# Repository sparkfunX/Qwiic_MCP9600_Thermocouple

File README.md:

SparkFun MCP9600 Thermocouple Amplifier
========================================

[*Thermocouple Amplifier (SPX-15508)*](https://www.sparkfun.com/products/15508)

The MCP9600 is an integrated thermocouple amplifier featuring a typical accuracy of ±0.5°C and a maximum accuracy of ±1.5°C, with support for many thermocouple types, conversion modes, and a configurable exponential moving average filter.

Repository Contents
-------------------

* **/Documentation** - Data sheets, additional product information
* **/Hardware** - Eagle design files (.brd, .sch)
* **/Production** - Production panel files (.brd)

Documentation
--------------
* **[SparkFun MCP9600 Arduino Library](https://github.com/sparkfun/SparkFun_MCP9600_Arduino_Library)** - Arduino library for the MCP9600.

License Information
-------------------

This product is _**open source**_! 

Please review the LICENSE.md file for license information. 

If you have any questions or concerns on licensing, please contact technical support on our [SparkFun forums](https://forum.sparkfun.com/viewforum.php?f=152).

Distributed as-is; no warranty is given.

- Your friends at SparkFun.

_<COLLABORATION CREDIT>_

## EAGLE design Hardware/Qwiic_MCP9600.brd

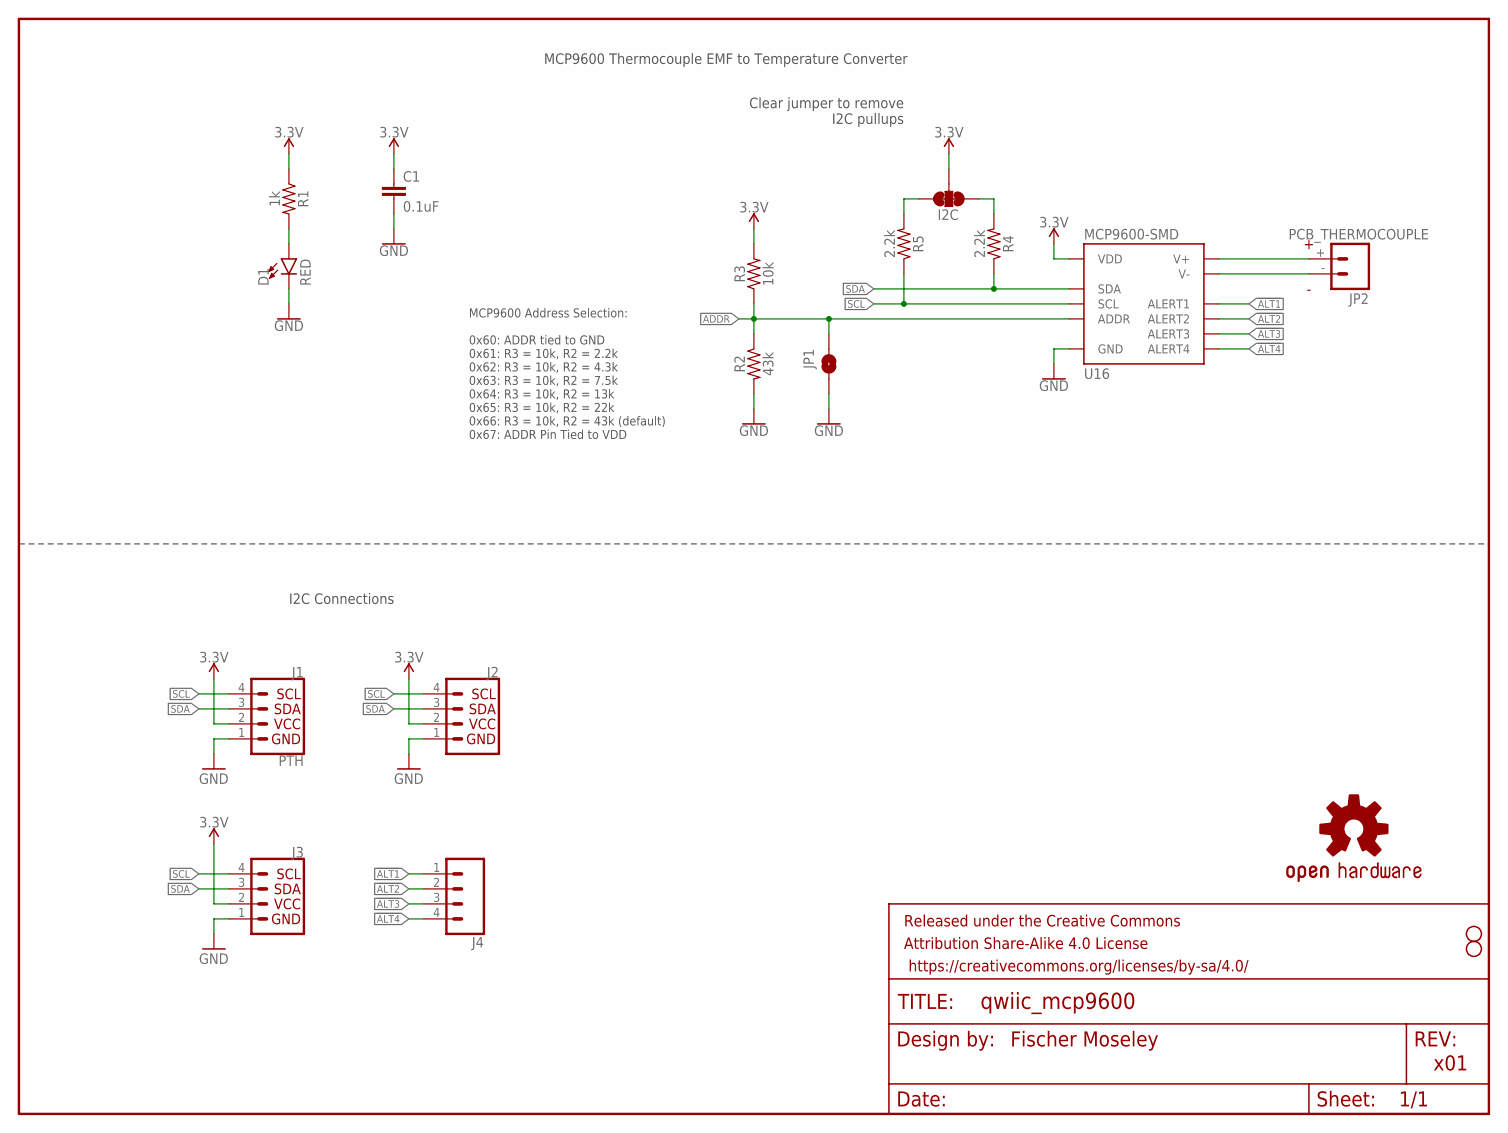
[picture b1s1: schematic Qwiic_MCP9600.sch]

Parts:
C1: 0.1uF; 0603
D1: RED; LED-0603
FRAME1: FRAME-LETTER; CREATIVE_COMMONS
I2C: JUMPER-SMT_3_2-NC_TRACE_SILK; SMT-JUMPER_3_2-NC_TRACE_SILK
J1: PTH; 1X04_NO_SILK
J2, J3: QWIIC_CONNECTORJS-1MM; JST04_1MM_RA
J4: CONN_041X04_NO_SILK; 1X04_NO_SILK
JP1: JUMPER-SMT_2_NO_SILK; SMT-JUMPER_2_NO_SILK
JP2: PCB_THERMOCOUPLE; PCC-SMP
JP8, JP9: STAND-OFF
LOGO1: OSHW-LOGOMINI; OSHW-LOGO-MINI
R1: 1k; 0603
R2: 43k; 0603
R3: 10k; 0603
R4, R5: 2.2k; 0603
U16: MCP9600-SMD; MQFN-20

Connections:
3.3V: C1.1, I2C.2, J1.2 (VCC), J2.2, J3.2, R1.1, R3.2, U16.8 (VDD)
!ALT1: J4.1, U16.11 (ALERT1)
!ALT2: J4.2, U16.12 (ALERT2)
!ALT3: J4.3, U16.14 (ALERT3)
!ALT4: J4.4, U16.15 (ALERT4)
ADDR: JP1.1, R2.1, R3.1, U16.16 (ADDR)
GND: C1.2, D1.C, J1.1 (GND), J2.1, J3.1, JP1.2, R2.2, U16.1 (GND), U16.3 (GND), U16.5 (GND), U16.6 (GND), U16.7 (GND), U16.9 (GND), U16.10 (GND), U16.13 (GND), U16.17 (GND), U16.18 (GND), U16.21 (GND)
unnamed: D1.A, R1.2
unnamed: I2C.1, R5.2
unnamed: I2C.3, R4.2
unnamed: JP2.+, U16.2 (V+)
unnamed: JP2.-, U16.4 (V-)
SCL: J1.4 (SCL), J2.4, J3.4, R5.1, U16.19 (SCL)
SDA: J1.3 (SDA), J2.3, J3.3, R4.1, U16.20 (SDA)

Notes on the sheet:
I2C Connections
MCP9600 Thermocouple EMF to Temperature Converter
Fischer Moseley
Clear jumper to remove I2C pullups
MCP9600 Address Selection: 0x60: ADDR tied to GND 0x61: R3 = 10k, R2 = 2.2k 0x62: R3 = 10k, R2 = 4.3k 0x63: R3 = 10k, R2 = 7.5k 0x64: R3 = 10k, R2 = 13k 0x65: R3 = 10k, R2 = 22k 0x66: R3 = 10k, R2 = 43k (default) 0x67: ADDR Pin Tied to VDD
x01

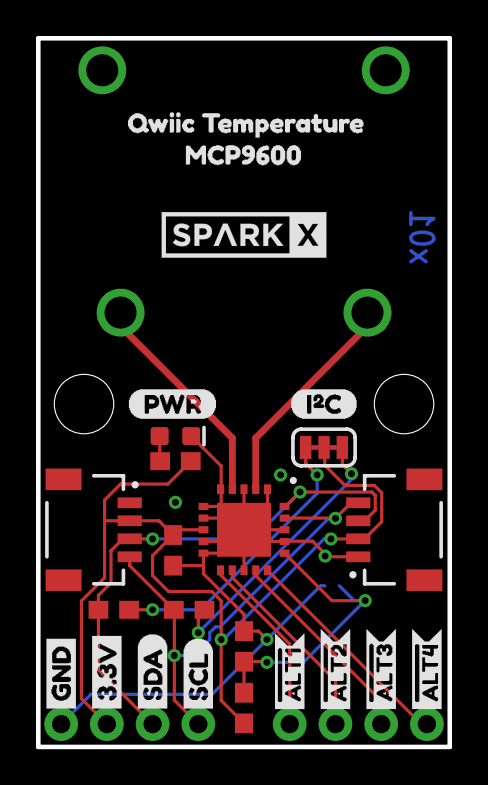
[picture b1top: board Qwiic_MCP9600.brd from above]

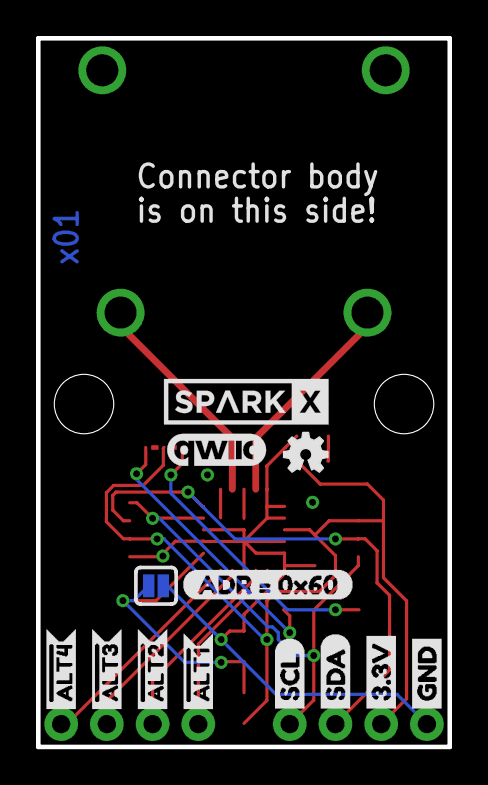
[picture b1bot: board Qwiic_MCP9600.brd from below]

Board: 2 copper layers, 22.9 x 39.4 mm, 43 parts (14 on the bottom side), 14 nets.

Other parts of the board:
U$1, U$5: #ALT30
U$2, U$17: SPARKX-MEDIUM
U$3, U$8: #ALT10
U$4, U$18: #ALT20
U$6: QWIIC_TEMPERATURE2
U$7, U$11: #ALT40
U$9, U$12: SCL-[)
U$10, U$23: GND-04
U$13, U$14: SDA-[)
U$15: QWIIC_5.5MM
U$19, U$22: 3.3V
U$20: PWR-()-04
U$21: I_SUPER2_C-()-04
U$25: MCP96000
U$27: ADR_#_0X600

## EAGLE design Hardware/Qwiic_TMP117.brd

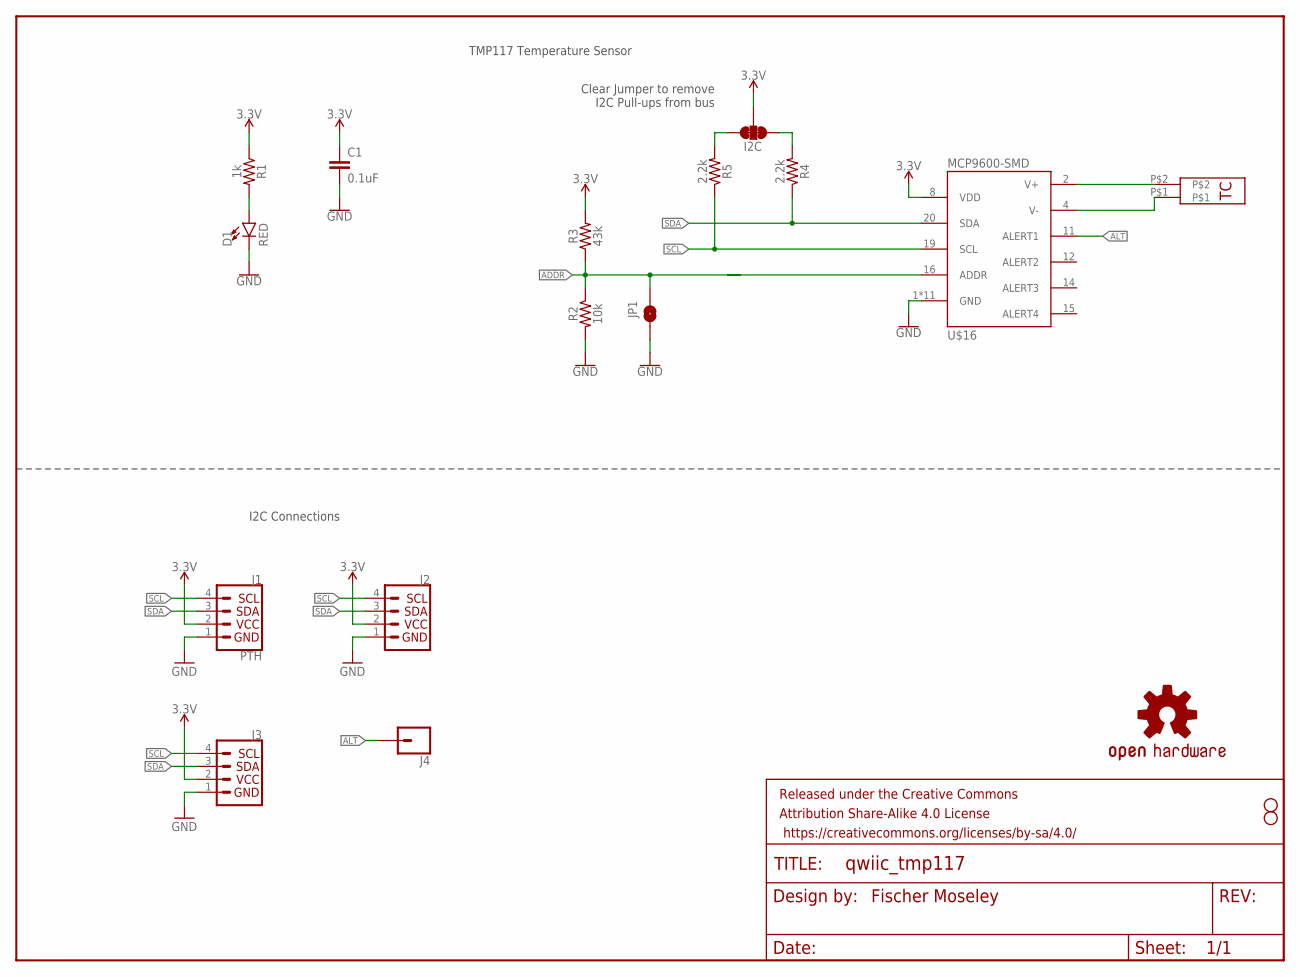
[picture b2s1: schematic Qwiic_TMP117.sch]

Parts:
C1: 0.1uF; 0603
D1: RED; LED-0603
FRAME1: FRAME-LETTER; CREATIVE_COMMONS
I2C: JUMPER-SMT_3_2-NC_TRACE_SILK; SMT-JUMPER_3_2-NC_TRACE_SILK
J1: PTH; 1X04_NO_SILK
J2, J3: QWIIC_CONNECTORJS-1MM; JST04_1MM_RA
J4: CONN_01PTH_NO_SILK_YES_STOP; 1X01_NO_SILK
JP1: JUMPER-SMT_2_NO_SILK; SMT-JUMPER_2_NO_SILK
JP8, JP9: STAND-OFF
LOGO1: OSHW-LOGOMINI; OSHW-LOGO-MINI
R1: 1k; 0603
R2: 10k; 0603
R3: 43k; 0603
R4, R5: 2.2k; 0603
U$16: MCP9600-SMD; MQFN-20
U$24: CHARLESPAX_TC-MINI-CONNECTOR

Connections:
3.3V: C1.1, I2C.2, J1.2 (VCC), J2.2, J3.2, R1.1, R3.2, U$16.8 (VDD)
ADDR: JP1.1, R2.1, R3.1, U$16.16 (ADDR)
ALT: J4.1, U$16.11 (ALERT1)
GND: C1.2, D1.C, J1.1 (GND), J2.1, J3.1, JP1.2, R2.2, U$16.1 (GND), U$16.3 (GND), U$16.5 (GND), U$16.6 (GND), U$16.7 (GND), U$16.9 (GND), U$16.10 (GND), U$16.13 (GND), U$16.17 (GND), U$16.18 (GND), U$16.21 (GND)
unnamed: D1.A, R1.2
unnamed: I2C.1, R5.2
unnamed: I2C.3, R4.2
unnamed: U$16.2 (V+), U$24.P$2
unnamed: U$16.4 (V-), U$24.P$1
SCL: J1.4 (SCL), J2.4, J3.4, R5.1, U$16.19 (SCL)
SDA: J1.3 (SDA), J2.3, J3.3, R4.1, U$16.20 (SDA)

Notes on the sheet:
I2C Connections
TMP117 Temperature Sensor
Fischer Moseley
Clear Jumper to remove I2C Pull-ups from bus

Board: 2 copper layers, 41 parts (14 on the bottom side), 11 nets, no tracks yet.

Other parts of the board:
U$1: 0X4B1
U$2, U$17: SPARKX-MEDIUM
U$3, U$11: INT#-[<-04
U$4: TMP1171
U$5: 0X4A0
U$6: QWIIC_TEMPERATURE2
U$7: INT-()-04
U$8: 0X493
U$9, U$12: SCL-[)
U$10, U$23: GND-04
U$13, U$14: SDA-[)
U$15: QWIIC_5.5MM
U$18: ADR_#_0X484
U$19, U$22: 3.3V
U$20: PWR-()-04
U$21: I_SUPER2_C-()-04

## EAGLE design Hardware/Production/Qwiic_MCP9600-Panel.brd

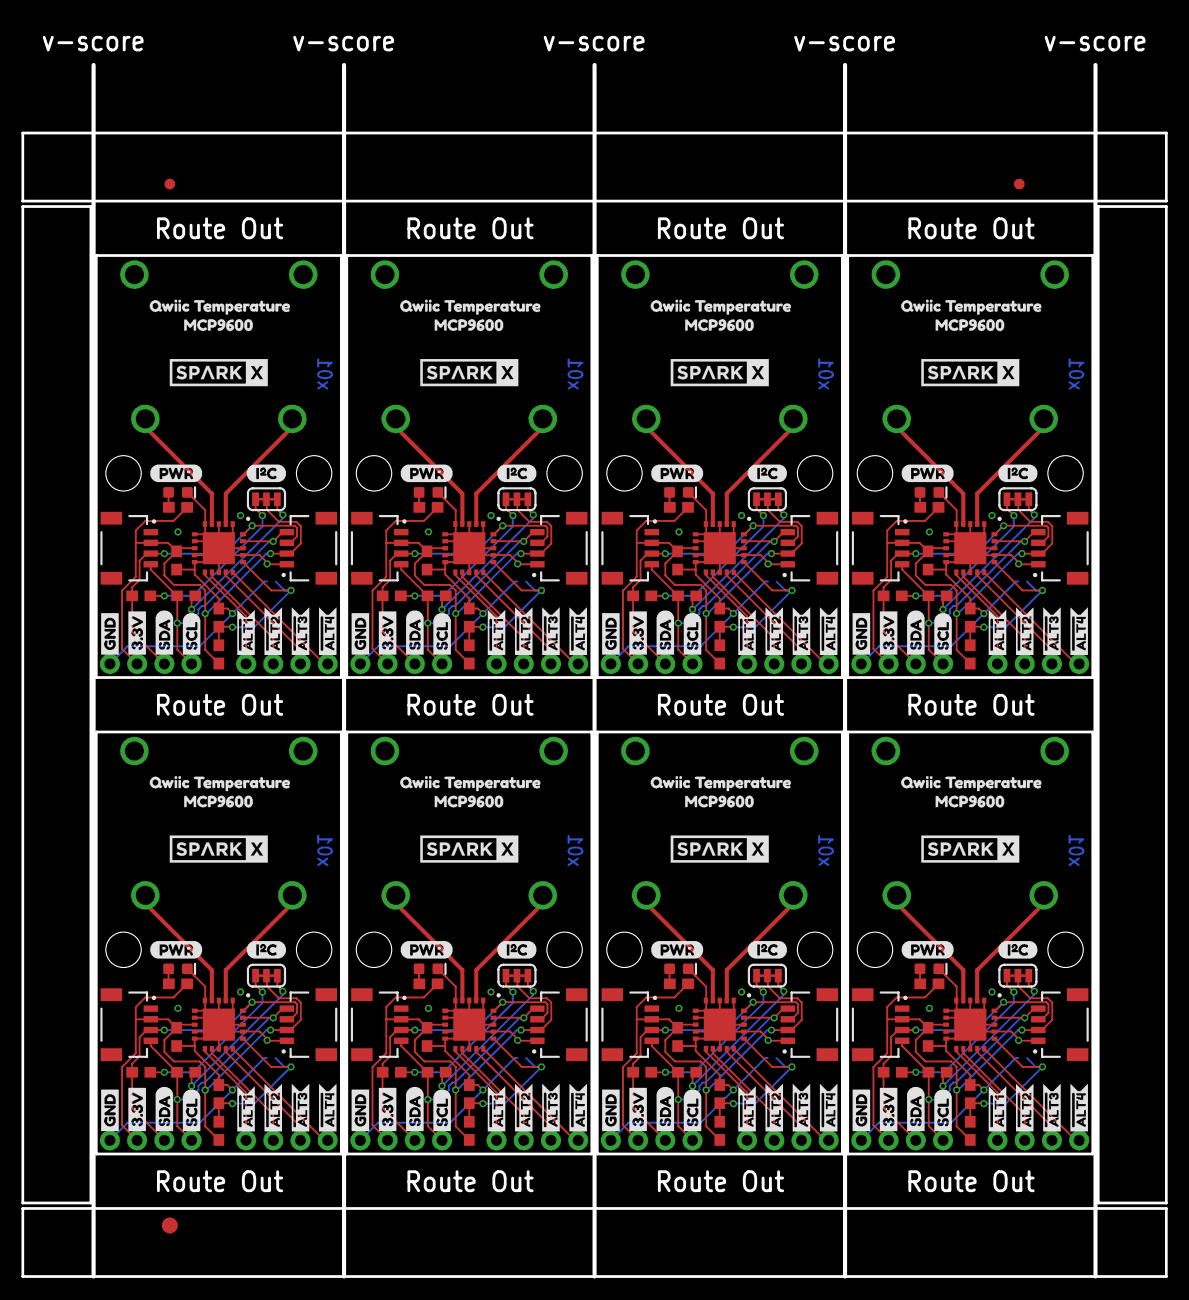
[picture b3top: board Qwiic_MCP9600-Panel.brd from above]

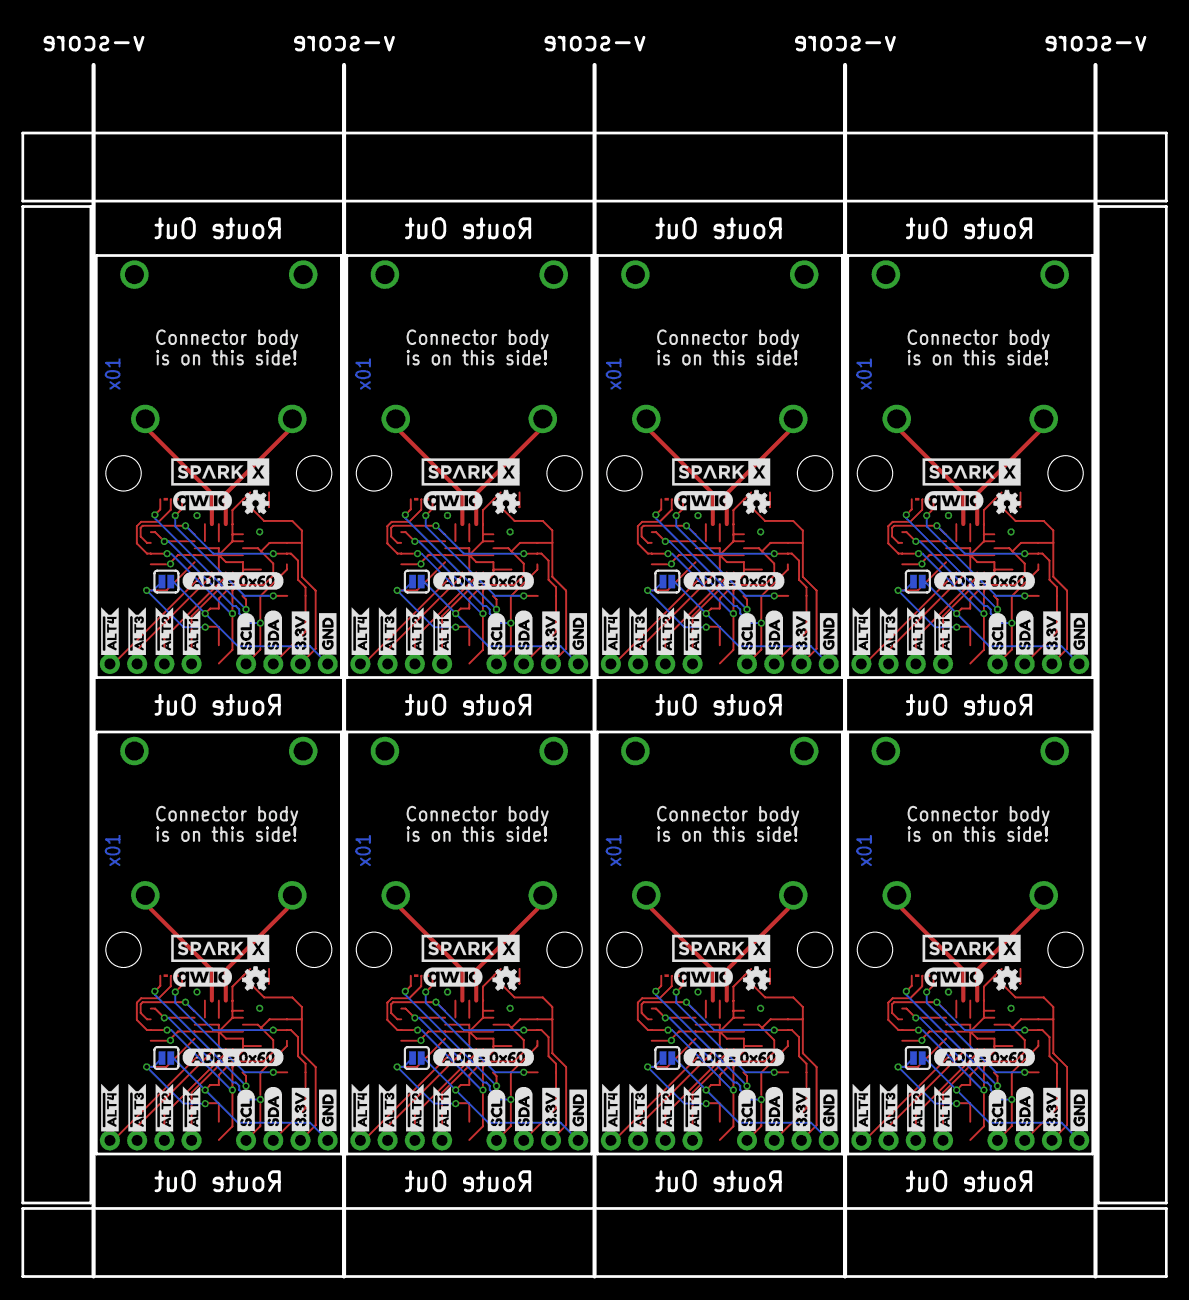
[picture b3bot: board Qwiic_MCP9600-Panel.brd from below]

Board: 2 copper layers, 106.6 x 116.9 mm, 339 parts (112 on the bottom side), 112 nets.

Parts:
C1, C2, C3, C4, C5, C6, C7, C8: 0.1uF; 0603
D1, D2, D3, D4, D5, D6, D7, D8: RED; LED-0603
E$1, E$2: FIDUCIAL-1X2
E$3: FIDUCIAL-1.5X3
I2C, I2C1, I2C2, I2C3, I2C4, I2C5, I2C6, I2C7: SMT-JUMPER_3_2-NC_TRACE_SILK
J1, J5, J9, J13, J17, J21, J25, J29: PTH; 1X04_NO_SILK
J2, J3, J6, J7, J10, J11, J14, J15, J18, J19, J22, J23, J26, J27, J30, J31: JST04_1MM_RA
J4, J8, J12, J16, J20, J24, J28, J32: 1X04_NO_SILK
JP1, JP3, JP7, JP13, JP17, JP21, JP25, JP29: SMT-JUMPER_2_NO_SILK
JP2, JP6, JP12, JP16, JP20, JP24, JP28, JP32: PCB_THERMOCOUPLE; PCC-SMP
JP4, JP5, JP8, JP9, JP10, JP11, JP14, JP15, JP18, JP19, JP22, JP23, JP26, JP27, JP30, JP31: STAND-OFF
LOGO1, LOGO2, LOGO3, LOGO4, LOGO5, LOGO6, LOGO7, LOGO8: OSHW-LOGOMINI; OSHW-LOGO-MINI
R1, R6, R11, R16, R21, R26, R31, R36: 1k; 0603
R2, R7, R12, R17, R22, R27, R32, R37: 43k; 0603
R3, R10, R15, R20, R25, R30, R35, R40: 10k; 0603
R4, R5, R8, R9, R13, R14, R18, R19, R23, R24, R28, R29, R33, R34, R38, R39: 2.2k; 0603
U1, U2, U3, U4, U5, U6, U7, U16: MCP9600-SMD; MQFN-20
U$1, U$5, U$43, U$47, U$67, U$71, U$91, U$95, U$115, U$119, U$139, U$143, U$163, U$167, U$187, U$191: #ALT30
U$2, U$17, U$24, U$26, U$50, U$51, U$74, U$75, U$98, U$99, U$122, U$123, U$146, U$147, U$170, U$171: SPARKX-MEDIUM
U$3, U$8, U$41, U$45, U$65, U$69, U$89, U$93, U$113, U$117, U$137, U$141, U$161, U$165, U$185, U$189: #ALT10
U$4, U$18, U$42, U$46, U$66, U$70, U$90, U$94, U$114, U$118, U$138, U$142, U$162, U$166, U$186, U$190: #ALT20
U$6, U$16, U$49, U$73, U$97, U$121, U$145, U$169: QWIIC_TEMPERATURE2
U$7, U$11, U$44, U$48, U$68, U$72, U$92, U$96, U$116, U$120, U$140, U$144, U$164, U$168, U$188, U$192: #ALT40
U$9, U$12, U$28, U$35, U$52, U$59, U$76, U$83, U$100, U$107, U$124, U$131, U$148, U$155, U$172, U$179: SCL-[)
U$10, U$23, U$33, U$34, U$57, U$58, U$81, U$82, U$105, U$106, U$129, U$130, U$153, U$154, U$177, U$178: GND-04
U$13, U$14, U$36, U$37, U$60, U$61, U$84, U$85, U$108, U$109, U$132, U$133, U$156, U$157, U$180, U$181: SDA-[)
U$15, U$38, U$62, U$86, U$110, U$134, U$158, U$182: QWIIC_5.5MM
U$19, U$22, U$31, U$32, U$55, U$56, U$79, U$80, U$103, U$104, U$127, U$128, U$151, U$152, U$175, U$176: 3.3V
U$20, U$29, U$53, U$77, U$101, U$125, U$149, U$173: PWR-()-04
U$21, U$30, U$54, U$78, U$102, U$126, U$150, U$174: I_SUPER2_C-()-04
U$25, U$39, U$63, U$87, U$111, U$135, U$159, U$183: MCP96000
U$27, U$40, U$64, U$88, U$112, U$136, U$160, U$184: ADR_#_0X600

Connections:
3.3V: C1.1, I2C.2, J1.2, J2.2, J3.2, R1.1, R3.2, U16.8
3.3V1: C2.1, I2C1.2, J5.2, J6.2, J7.2, R6.1, R10.2, U1.8
3.3V2: C3.1, I2C2.2, J9.2, J10.2, J11.2, R11.1, R15.2, U2.8
3.3V3: C4.1, I2C3.2, J13.2, J14.2, J15.2, R16.1, R20.2, U3.8
3.3V4: C5.1, I2C4.2, J17.2, J18.2, J19.2, R21.1, R25.2, U4.8
3.3V5: C6.1, I2C5.2, J21.2, J22.2, J23.2, R26.1, R30.2, U5.8
3.3V6: C7.1, I2C6.2, J25.2, J26.2, J27.2, R31.1, R35.2, U6.8
3.3V7: C8.1, I2C7.2, J29.2, J30.2, J31.2, R36.1, R40.2, U7.8
!ALT1: J4.1, U16.11
!ALT2: J4.2, U16.12
!ALT3: J4.3, U16.14
!ALT4: J4.4, U16.15
!ALT5: J8.1, U1.11
!ALT6: J8.3, U1.14
!ALT7: J8.4, U1.15
!ALT8: J8.2, U1.12
!ALT9: J12.1, U2.11
!ALT10: J12.3, U2.14
!ALT11: J12.4, U2.15
!ALT12: J12.2, U2.12
!ALT13: J16.1, U3.11
!ALT14: J16.3, U3.14
!ALT15: J16.4, U3.15
!ALT16: J16.2, U3.12
!ALT17: J20.1, U4.11
!ALT18: J20.3, U4.14
!ALT19: J20.4, U4.15
!ALT20: J20.2, U4.12
!ALT21: J24.1, U5.11
!ALT22: J24.3, U5.14
!ALT23: J24.4, U5.15
!ALT24: J24.2, U5.12
!ALT25: J28.1, U6.11
!ALT26: J28.3, U6.14
!ALT27: J28.4, U6.15
!ALT28: J28.2, U6.12
!ALT29: J32.1, U7.11
!ALT30: J32.3, U7.14
!ALT31: J32.4, U7.15
!ALT32: J32.2, U7.12
ADDR: JP1.1, R2.1, R3.1, U16.16
ADDR1: JP3.1, R7.1, R10.1, U1.16
ADDR2: JP7.1, R12.1, R15.1, U2.16
ADDR3: JP13.1, R17.1, R20.1, U3.16
ADDR4: JP17.1, R22.1, R25.1, U4.16
ADDR5: JP21.1, R27.1, R30.1, U5.16
ADDR6: JP25.1, R32.1, R35.1, U6.16
ADDR7: JP29.1, R37.1, R40.1, U7.16
GND: C1.2, D1.C, J1.1, J2.1, J3.1, JP1.2, R2.2, U16.1, U16.3, U16.5, U16.6, U16.7, U16.9, U16.10, U16.13, U16.17, U16.18, U16.21
GND1: C2.2, D2.C, J5.1, J6.1, J7.1, JP3.2, R7.2, U1.1, U1.3, U1.5, U1.6, U1.7, U1.9, U1.10, U1.13, U1.17, U1.18, U1.21
GND2: C3.2, D3.C, J9.1, J10.1, J11.1, JP7.2, R12.2, U2.1, U2.3, U2.5, U2.6, U2.7, U2.9, U2.10, U2.13, U2.17, U2.18, U2.21
GND3: C4.2, D4.C, J13.1, J14.1, J15.1, JP13.2, R17.2, U3.1, U3.3, U3.5, U3.6, U3.7, U3.9, U3.10, U3.13, U3.17, U3.18, U3.21
GND4: C5.2, D5.C, J17.1, J18.1, J19.1, JP17.2, R22.2, U4.1, U4.3, U4.5, U4.6, U4.7, U4.9, U4.10, U4.13, U4.17, U4.18, U4.21
GND5: C6.2, D6.C, J21.1, J22.1, J23.1, JP21.2, R27.2, U5.1, U5.3, U5.5, U5.6, U5.7, U5.9, U5.10, U5.13, U5.17, U5.18, U5.21
GND6: C7.2, D7.C, J25.1, J26.1, J27.1, JP25.2, R32.2, U6.1, U6.3, U6.5, U6.6, U6.7, U6.9, U6.10, U6.13, U6.17, U6.18, U6.21
GND7: C8.2, D8.C, J29.1, J30.1, J31.1, JP29.2, R37.2, U7.1, U7.3, U7.5, U7.6, U7.7, U7.9, U7.10, U7.13, U7.17, U7.18, U7.21
unnamed: D1.A, R1.2
unnamed: I2C.1, R5.2
unnamed: I2C.3, R4.2
unnamed: JP2.+, U16.2
unnamed: JP2.-, U16.4
unnamed: D2.A, R6.2
unnamed: I2C1.1, R9.2
unnamed: I2C1.3, R8.2
unnamed: JP6.+, U1.2
unnamed: JP6.-, U1.4
unnamed: D3.A, R11.2
unnamed: I2C2.1, R14.2
unnamed: I2C2.3, R13.2
unnamed: JP12.+, U2.2
unnamed: JP12.-, U2.4
unnamed: D4.A, R16.2
unnamed: I2C3.1, R19.2
unnamed: I2C3.3, R18.2
unnamed: JP16.+, U3.2
unnamed: JP16.-, U3.4
unnamed: D5.A, R21.2
unnamed: I2C4.1, R24.2
unnamed: I2C4.3, R23.2
unnamed: JP20.+, U4.2
unnamed: JP20.-, U4.4
unnamed: D6.A, R26.2
unnamed: I2C5.1, R29.2
unnamed: I2C5.3, R28.2
unnamed: JP24.+, U5.2
unnamed: JP24.-, U5.4
unnamed: D7.A, R31.2
unnamed: I2C6.1, R34.2
unnamed: I2C6.3, R33.2
unnamed: JP28.+, U6.2
unnamed: JP28.-, U6.4
unnamed: D8.A, R36.2
unnamed: I2C7.1, R39.2
unnamed: I2C7.3, R38.2
unnamed: JP32.+, U7.2
unnamed: JP32.-, U7.4
SCL: J1.4, J2.4, J3.4, R5.1, U16.19
SCL1: J5.4, J6.4, J7.4, R9.1, U1.19
SCL2: J9.4, J10.4, J11.4, R14.1, U2.19
SCL3: J13.4, J14.4, J15.4, R19.1, U3.19
SCL4: J17.4, J18.4, J19.4, R24.1, U4.19
SCL5: J21.4, J22.4, J23.4, R29.1, U5.19
SCL6: J25.4, J26.4, J27.4, R34.1, U6.19
SCL7: J29.4, J30.4, J31.4, R39.1, U7.19
SDA: J1.3, J2.3, J3.3, R4.1, U16.20
SDA1: J5.3, J6.3, J7.3, R8.1, U1.20
SDA2: J9.3, J10.3, J11.3, R13.1, U2.20
SDA3: J13.3, J14.3, J15.3, R18.1, U3.20
SDA4: J17.3, J18.3, J19.3, R23.1, U4.20
SDA5: J21.3, J22.3, J23.3, R28.1, U5.20
SDA6: J25.3, J26.3, J27.3, R33.1, U6.20
SDA7: J29.3, J30.3, J31.3, R38.1, U7.20

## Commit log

2019-06-14 Import directory structure
2019-06-14 Added datasheet, removed extraneous README's
2019-06-14 Library created, schematic ready for review, began layout
2019-06-17 Push before initial layout review
2019-06-18 Push changes made after first layout review
2019-06-18 Changed MCP9600 designator
    U$16 -> U16
2019-06-18 Added addressing information to schematic
2019-07-01 Added production files
2019-07-22 Updated readme, fixed directory structure
2019-07-22 Removed the cat .gif from the readme
    Press F to pay respects to our fallen comrade.
2020-02-13 Add test sketch

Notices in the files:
parts and their libraries:
SparkFun-Capacitors: Licensing: Creative Commons ShareAlike 4.0 International - https://creativecommons.org/licenses/by-sa/4.0
SparkFun-Aesthetics: Released under the Creative Commons Attribution Share-Alike 4.0 License
SparkFun-Aesthetics: https://creativecommons.org/licenses/by-sa/4.0
